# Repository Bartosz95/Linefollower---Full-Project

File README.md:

# Linefollowers

# Abstract 
Current repository contains three of my line follower projects.
Linefollower is a mobile robot which follows the line.
My robots were built for competitions so the main aim was to allow them to move fast.
Some of them were also remote controlled.
I've created these robots from top to bottom myself it means that I designed a board, created it, solder elements, create program for CPU and install it.

# Technologies
- KiCad
- STM32CubeMX
- Qt

# Description
As I mentioned current directory contains three robots
- BEBO - my first line follower which has PID algorithm
- LFANT - line follower which has spread encoders and mesure his speed
- Remote Controlled - this one is controlled by desktop remote app
To create these robots I had to do the same steps which I described below.

## Hardware
First I have to design a board. I've used a KiCad application to do it.
During this process I had to choose a CPU, engines, bridge for engine, battery, line sensors and all necessary elements.
I have chosen CPU STM32F051C8Tx because is enough small, 2 Pololu 10:1 engines, TB6612 bridge, Li-Pol 7,4V battery, line sensor KTIR0711s and depending on project AS5048A encoders or HC-06 bluetooth module.
Below you can see what it looks like designed boards ready to create.

In the next step I have to create this board and solder elements.
All

## Software
For creating software I decided to use the STM32CubeMX application.
It allows you to create programs for STM processors easily.
I assigned all necessary pins to the processor and created a controlled program.
When I finished programming it, I installed a program on robots by programator located on the STM32F4 board.
Created connection looks like below.

Ready robot looks like below.

# Desktop application
For a remote controlled robot I created a program in C++ Qt. 
The connection works through bluetooth. Program works below.
The main window of the program is split vertically.
On the left side you can see measurements from the line follower.
On the right you have a control panel.
If each sensor detects a black line the circle of the top will change to black.
Below grey rectangles you can see 0. When a robot is moving it shows speed in mps.
In the control panel you have 5 buttons.
The one on the top change remote controlling to automatic control by PID algorithm,
The next four allow remote control robots.

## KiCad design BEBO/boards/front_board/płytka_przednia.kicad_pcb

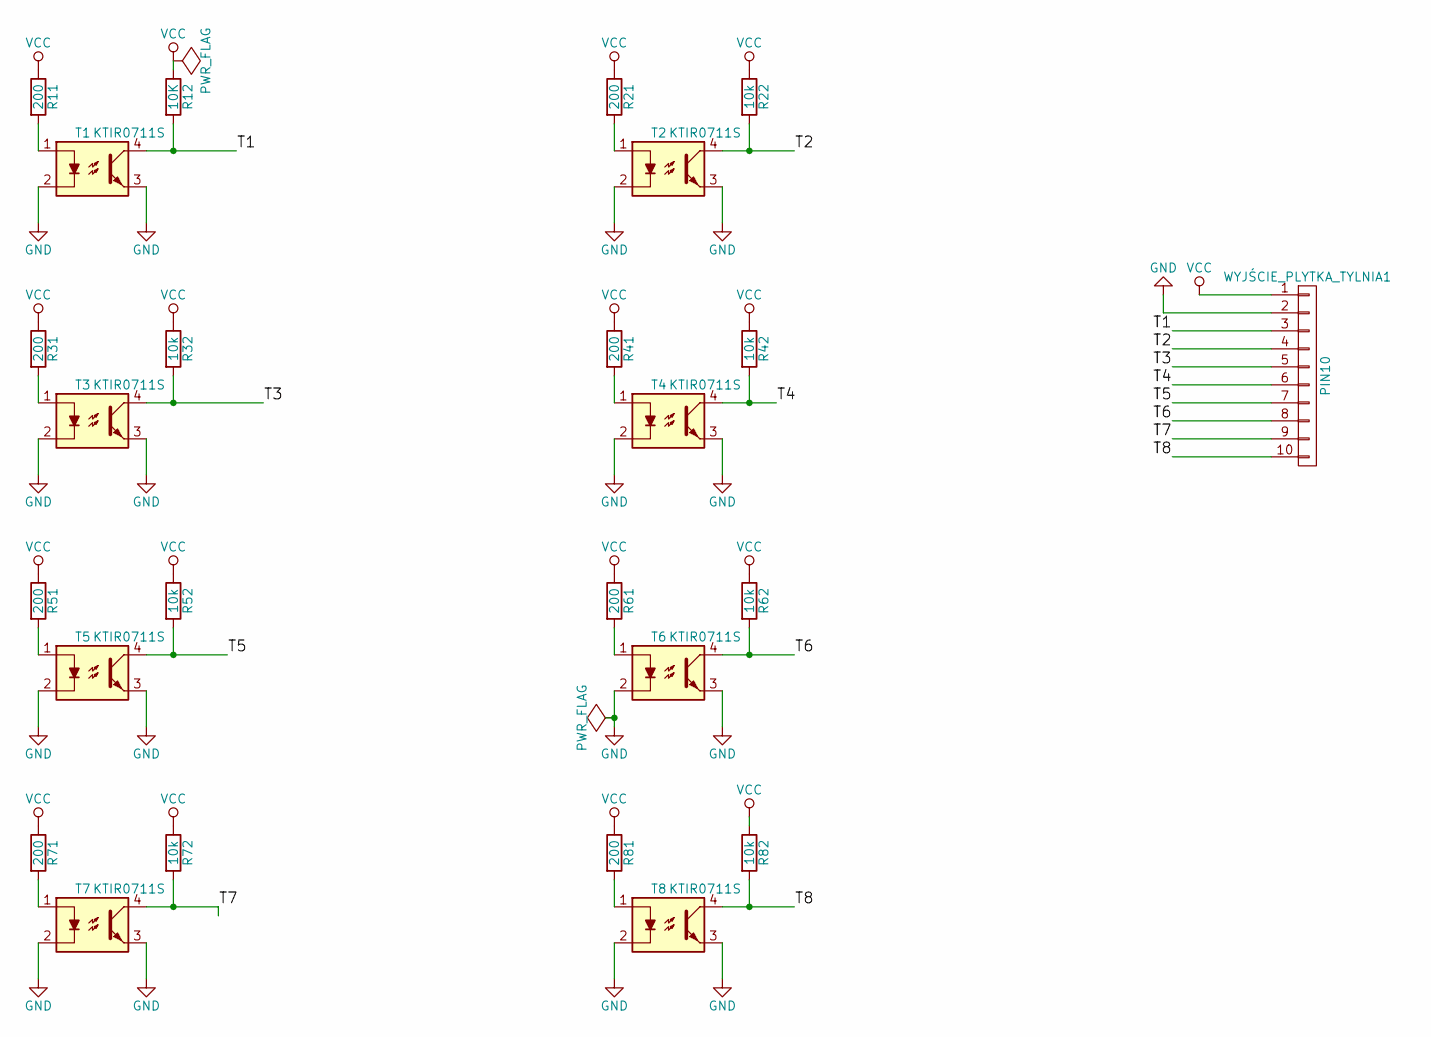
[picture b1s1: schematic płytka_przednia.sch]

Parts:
R11, R21, R31, R41, R51, R61, R71, R81: 200; R_0805_HandSoldering
R12: 10K; R_0805_HandSoldering
R22, R32, R42, R52, R62, R72, R82: 10k; R_0805_HandSoldering
T1, T2, T3, T4, T5, T6, T7, T8: KTIR0711S
WYJŚCIE_PLYTKA_TYLNIA1: PIN10; fpc_10_pin

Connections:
/T1: R12.2, T1.4, WYJŚCIE_PLYTKA_TYLNIA1.3
/T2: R22.2, T2.4, WYJŚCIE_PLYTKA_TYLNIA1.4
/T3: R32.2, T3.4, WYJŚCIE_PLYTKA_TYLNIA1.5
/T4: R42.2, T4.4, WYJŚCIE_PLYTKA_TYLNIA1.6
/T5: R52.2, T5.4, WYJŚCIE_PLYTKA_TYLNIA1.7
/T6: R62.2, T6.4, WYJŚCIE_PLYTKA_TYLNIA1.8
/T7: R72.2, T7.4, WYJŚCIE_PLYTKA_TYLNIA1.9
/T8: R82.2, T8.4, WYJŚCIE_PLYTKA_TYLNIA1.10
GND: T1.2, T1.3, T2.2, T2.3, T3.2, T3.3, T4.2, T4.3, T5.2, T5.3, T6.2, T6.3, T7.2, T7.3, T8.2, T8.3, WYJŚCIE_PLYTKA_TYLNIA1.2
unnamed: R11.2, T1.1
unnamed: R21.2, T2.1
unnamed: R31.2, T3.1
unnamed: R41.2, T4.1
unnamed: R51.2, T5.1
unnamed: R61.2, T6.1
unnamed: R71.2, T7.1
unnamed: R81.2, T8.1
VCC: R11.1, R12.1, R21.1, R22.1, R31.1, R32.1, R41.1, R42.1, R51.1, R52.1, R61.1, R62.1, R71.1, R72.1, R81.1, R82.1, WYJŚCIE_PLYTKA_TYLNIA1.1

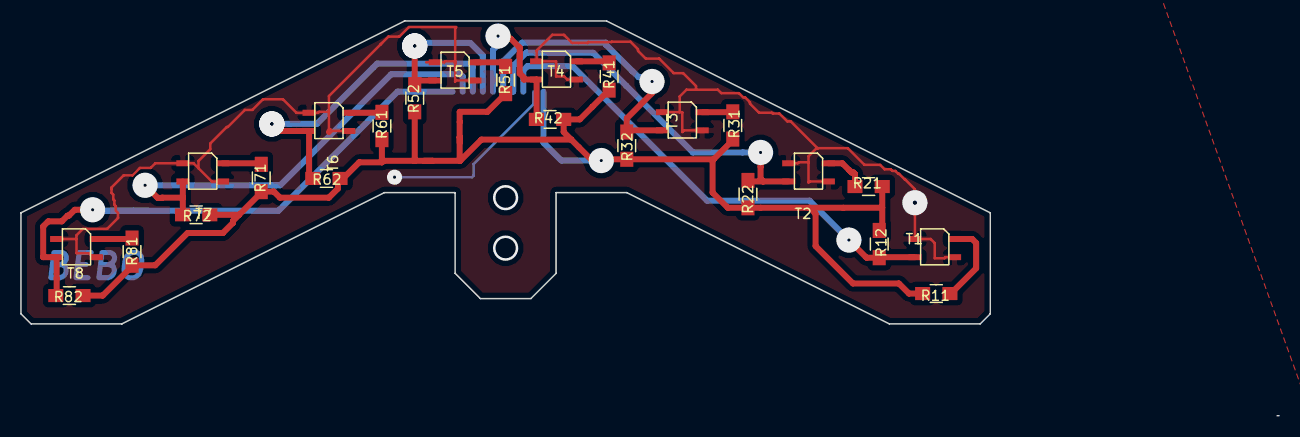
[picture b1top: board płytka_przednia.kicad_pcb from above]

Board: 2 copper layers, 124.6 x 39.1 mm, 25 parts (1 on the bottom side), 18 nets.

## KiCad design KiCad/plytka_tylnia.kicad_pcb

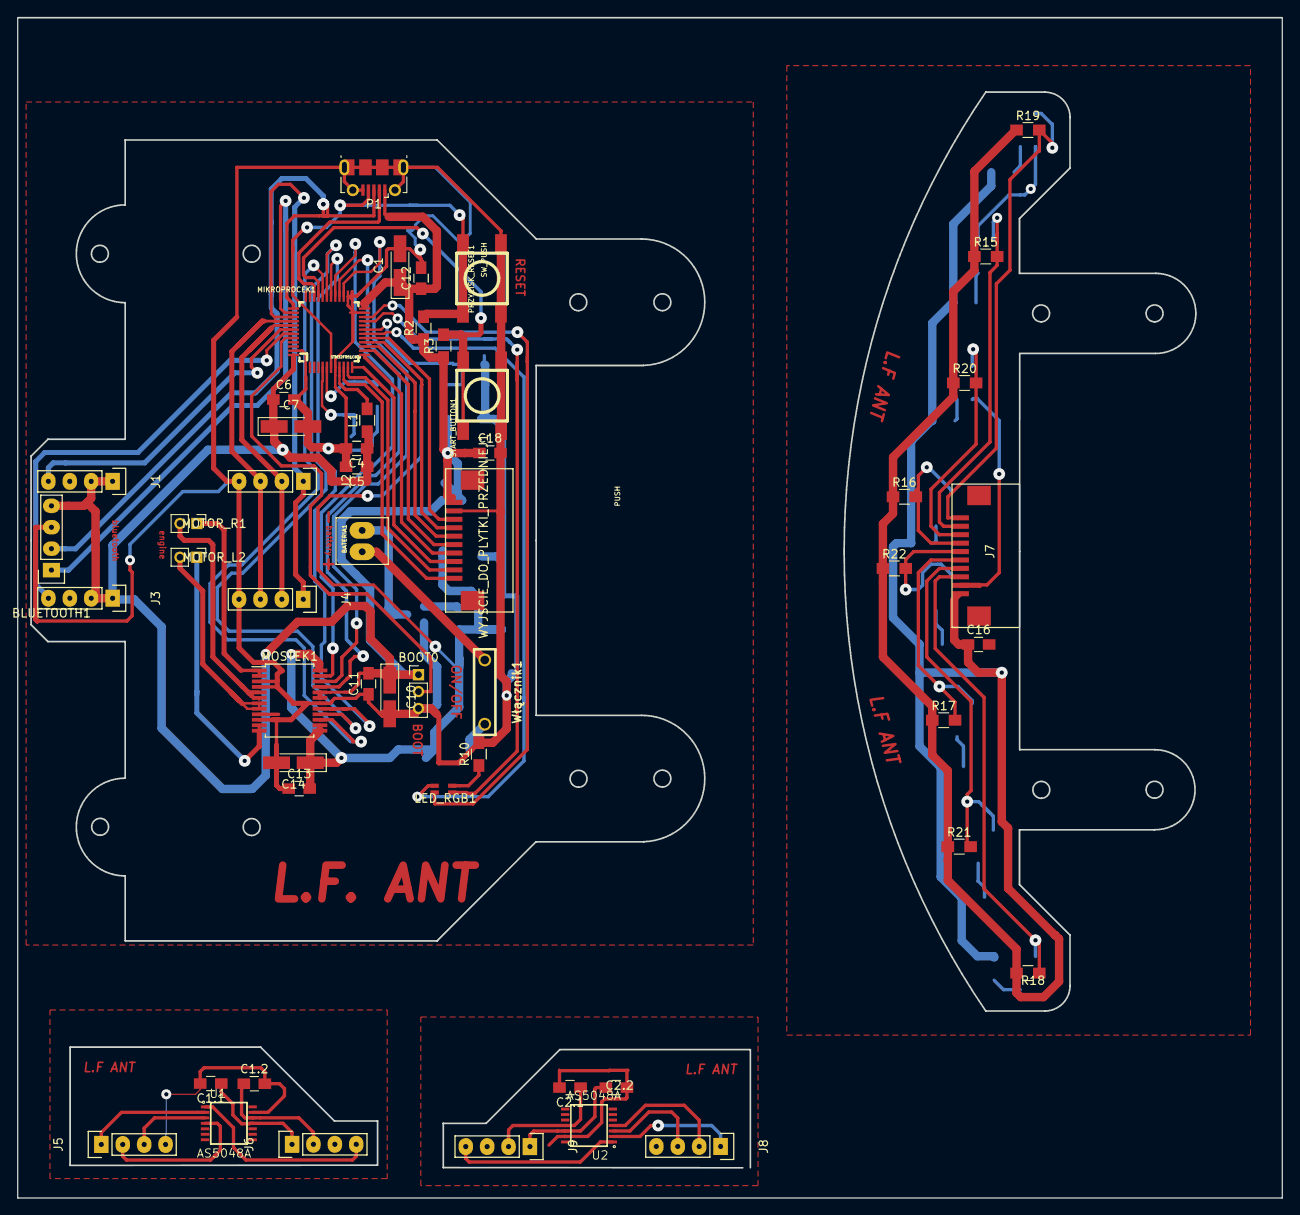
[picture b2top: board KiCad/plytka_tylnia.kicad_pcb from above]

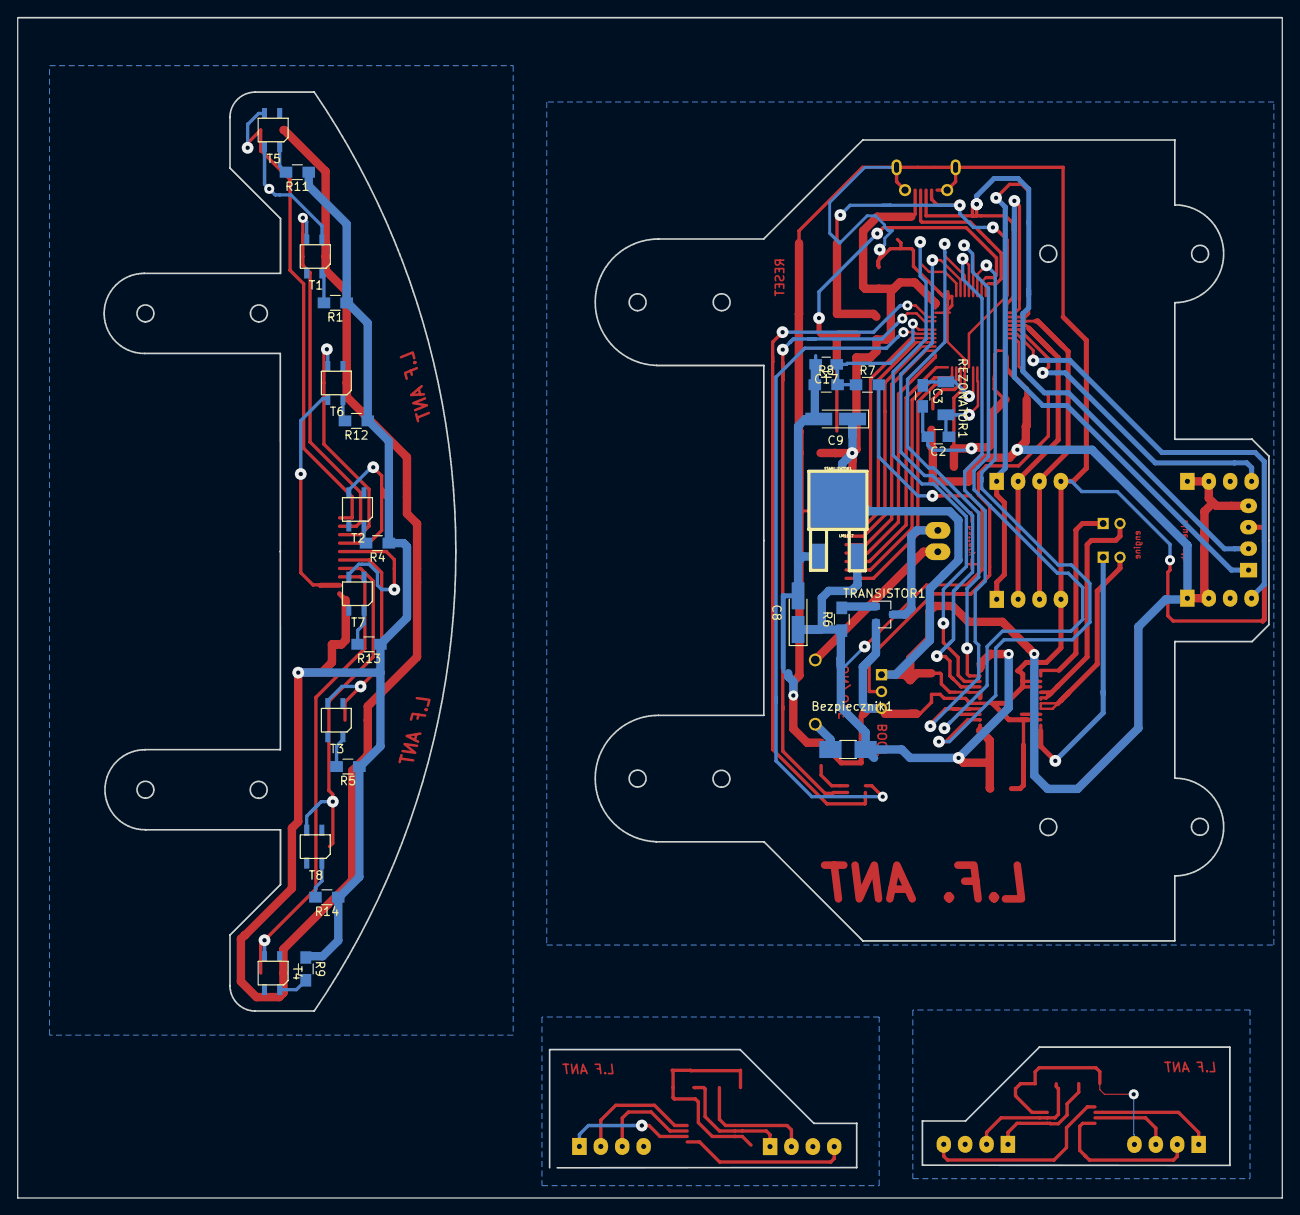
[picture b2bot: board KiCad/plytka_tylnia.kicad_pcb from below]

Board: 2 copper layers, 150.0 x 140.0 mm, 80 parts (28 on the bottom side), 72 nets.

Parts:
BATERIA1: LI-POL; zl_zasilania
BLUETOOTH1: PIN4; GoldPin_1x4
BOOT0: SWITCH; Pin_Header_Straight_1x03_Pitch2.00mm
Bezpiecznik1: Fuse ??; Fuse_SMD1206_HandSoldering
C1, C7: 4,7uF; CP_Tantalum_Case-A_EIA-3216-18_Hand
C1.1, C1.2, C2.1, C2.2, C16, C17: C; C_0805_HandSoldering
C2, C3: 22pF; C_0805_HandSoldering
C4: 10nF; C_0805_HandSoldering
C5: 1uF; C_0805_HandSoldering
C6, C11, C12, C13, C18: 100nF; C_0805_HandSoldering
C8, C9, C10, C14: 10uF; CP_Tantalum_Case-A_EIA-3216-18_Hand
J1, J2, J3, J4, J5, J6, J8, J9: CONN_01X04; GoldPin_1x4
J7: PIN10; fpc_10_pin
L1: 10uH; R_0805_HandSoldering
LED_RGB1: LED_CRGB; LED_RGB_0805
MIKROPROCEK1: STM32F051C8Tx; LQFP48
MOSTEK1: TB6612
MOTOR_L2: PIN2; Pin_Header_Straight_1x02_Pitch2.00mm
MOTOR_R1: PIN2; Pin_Header_Straight_1x02_Pitch2.00mm
P1: USB_OTG; USB_Micro-B_Molex-105017-0001
PRZYCISK_RESET1: SW_PUSH; SW_06_SMD
R1, R4, R5, R9, R11, R12, R13, R14: 200; R_0805_HandSoldering
R2, R3, R15, R16, R17, R18, R20, R21, R22: 10k; R_0805_HandSoldering
R6: 1k; R_0805_HandSoldering
R7: 51k; R_0805_HandSoldering
R8: 33k; R_0805_HandSoldering
R10: 220R; R_0805_HandSoldering
R19: 10K; R_0805_HandSoldering
REZONATOR1: HC49-S; Kwarc_SMD_Mini
STABILIZATOR1: LM1117; LM1117_TO-252
START_BUTTON1: PUSH; SW_06_SMD
T1, T2, T3, T4, T5, T6, T7, T8: KTIR0711S
TRANSISTOR1: BUZ11; SOT-23
U1, U2: AS5048A; SOP65P640X120-14N
WYJSCIE_DO_PLYTKI_PRZEDNIEJ1: PIN10; fpc_10_pin
Włącznik1: switch; dip_switch_1

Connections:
/3.31: C1.1.1, C1.2.1, J6.1, J6.2, U1.11, U1.12
/3.32: C2.1.1, C2.2.1, J9.1, J9.2, U2.11, U2.12
/BATERIA: Bezpiecznik1.1, C8.1, C13.2, C14.1, MOSTEK1.13, MOSTEK1.14, MOSTEK1.24, R6.1, R7.2, STABILIZATOR1.1
/BOOT0: BOOT0.2, MIKROPROCEK1.44
/CLK1: J5.1, U1.2
/CLK2: J8.1, U2.2
/GND1: C1.1.2, C1.2.2, J5.4, U1.13
/GND2: C2.1.2, C2.2.2, J8.4, U2.13
/LED_B: LED_RGB1.4, MIKROPROCEK1.18
/LED_G: LED_RGB1.3, MIKROPROCEK1.22
/LED_R: LED_RGB1.2, MIKROPROCEK1.21
/LIPOL_POMIAR: C17.1, MIKROPROCEK1.19, R7.1, R8.2
/L_1: MIKROPROCEK1.27, MOSTEK1.22
/L_2: MIKROPROCEK1.28, MOSTEK1.21
/L_PWM: MIKROPROCEK1.29, MOSTEK1.23
/MISO1: J5.3, U1.3
/MISO2: J8.3, U2.3
/MOSI1: J5.2, U1.4
/MOSI2: J8.2, U2.4
/RESET: MIKROPROCEK1.7, P1.4, PRZYCISK_RESET1.1, R2.2
/R_1: MIKROPROCEK1.31, MOSTEK1.16
/R_2: MIKROPROCEK1.30, MOSTEK1.17
/R_PWM: MIKROPROCEK1.32, MOSTEK1.15
/SPI1_CLK: J2.1, J4.1, MIKROPROCEK1.39
/SPI1_MISO: J2.3, J4.3, MIKROPROCEK1.40
/SPI1_MOSI: J2.2, J4.2, MIKROPROCEK1.41
/SPI1_SS1: J1.4, MIKROPROCEK1.42
/SPI1_SS2: J3.4, MIKROPROCEK1.43
/SS1: J6.4, U1.1
/SS2: J9.4, U2.1
/SWCLK: BLUETOOTH1.2, MIKROPROCEK1.37, P1.3
/SWDIO: MIKROPROCEK1.34, P1.2
/T1: MIKROPROCEK1.10, WYJSCIE_DO_PLYTKI_PRZEDNIEJ1.1
/T1P: J7.10, R19.2, T5.4
/T2: MIKROPROCEK1.11, WYJSCIE_DO_PLYTKI_PRZEDNIEJ1.2
/T2P: J7.9, R15.2, T1.4
/T3: MIKROPROCEK1.12, WYJSCIE_DO_PLYTKI_PRZEDNIEJ1.3
/T3P: J7.8, R20.2, T6.4
/T4: MIKROPROCEK1.13, WYJSCIE_DO_PLYTKI_PRZEDNIEJ1.4
/T4P: J7.7, R16.2, T2.4
/T5: MIKROPROCEK1.14, WYJSCIE_DO_PLYTKI_PRZEDNIEJ1.5
/T5P: J7.6, R22.2, T7.4
/T6: MIKROPROCEK1.15, WYJSCIE_DO_PLYTKI_PRZEDNIEJ1.6
/T6P: J7.5, R17.2, T3.4
/T7: MIKROPROCEK1.16, WYJSCIE_DO_PLYTKI_PRZEDNIEJ1.7
/T7P: J7.4, R21.2, T8.4
/T8: MIKROPROCEK1.17, WYJSCIE_DO_PLYTKI_PRZEDNIEJ1.8
/T8P: J7.3, R18.2, T4.4
/USART_RX: BLUETOOTH1.1, MIKROPROCEK1.38
GND: BLUETOOTH1.3, BOOT0.3, C1.2, C2.2, C3.2, C4.2, C5.2, C6.2, C7.2, C8.2, C9.2, C10.2, C11.1, C12.2, C13.1, C14.2, C16.2, C17.2, C18.2, J2.4, J4.4, J7.2, MIKROPROCEK1.1, MIKROPROCEK1.8, MIKROPROCEK1.23, MIKROPROCEK1.25, MIKROPROCEK1.26, MIKROPROCEK1.47, MOSTEK1.3, MOSTEK1.4, MOSTEK1.9, MOSTEK1.10, MOSTEK1.18, P1.5, P1.6, PRZYCISK_RESET1.2, R8.1, R10.2, STABILIZATOR1.3, START_BUTTON1.1, T1.2, T1.3, T2.2, T2.3, T3.2, T3.3, T4.2, T4.3, T5.2, T5.3, T6.2, T6.3, T7.2, T7.3, T8.2, T8.3, TRANSISTOR1.2, WYJSCIE_DO_PLYTKI_PRZEDNIEJ1.9
unnamed: BATERIA1.1, TRANSISTOR1.3
unnamed: BATERIA1.2, Włącznik1.1
unnamed: Bezpiecznik1.2, Włącznik1.2
unnamed: C2.1, MIKROPROCEK1.5, REZONATOR1.2
unnamed: C3.1, MIKROPROCEK1.6, REZONATOR1.1
unnamed: L1.2, MIKROPROCEK1.9
unnamed: LED_RGB1.1, R10.1
unnamed: MIKROPROCEK1.33, R3.2, START_BUTTON1.2
unnamed: MOSTEK1.1, MOSTEK1.2, MOTOR_R1.1
unnamed: MOSTEK1.5, MOSTEK1.6, MOTOR_R1.2
unnamed: MOSTEK1.7, MOSTEK1.8, MOTOR_L2.2
unnamed: MOSTEK1.11, MOSTEK1.12, MOTOR_L2.1
unnamed: R1.2, T1.1
unnamed: R4.2, T2.1
unnamed: R5.2, T3.1
unnamed: R6.2, TRANSISTOR1.1
unnamed: R9.2, T4.1
unnamed: R11.2, T5.1
unnamed: R12.2, T6.1
unnamed: R13.2, T7.1
unnamed: R14.2, T8.1
VCC: BLUETOOTH1.4, BOOT0.1, C1.1, C4.1, C5.1, C6.1, C7.1, C9.1, C10.1, C11.2, C12.1, C16.1, C18.1, J1.1, J1.2, J3.1, J3.2, J7.1, L1.1, MIKROPROCEK1.24, MIKROPROCEK1.48, MOSTEK1.19, MOSTEK1.20, P1.1, R1.1, R2.1, R3.1, R4.1, R5.1, R9.1, R11.1, R12.1, R13.1, R14.1, R15.1, R16.1, R17.1, R18.1, R19.1, R20.1, R21.1, R22.1, STABILIZATOR1.2, WYJSCIE_DO_PLYTKI_PRZEDNIEJ1.10

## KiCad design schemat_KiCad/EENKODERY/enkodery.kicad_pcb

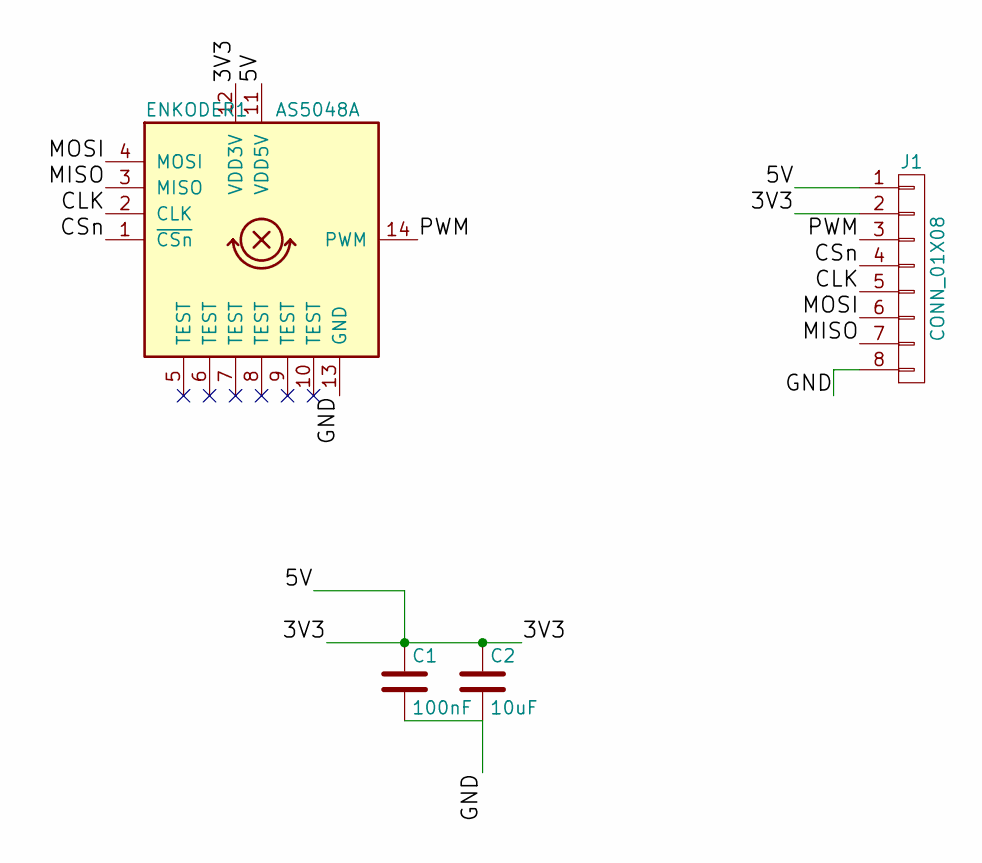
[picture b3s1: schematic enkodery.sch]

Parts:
C1: 100nF; C_0805_HandSoldering
C2: 10uF; C_0805_HandSoldering
ENKODER1: AS5048A; SOP65P640X120-14N
J1: CONN_01X08; Pin_Header_Straight_1x08_Pitch2.00mm

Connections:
/3V3: C1.1, C2.1, ENKODER1.11 (VDD5V), ENKODER1.12 (VDD3V), J1.1, J1.2
/CLK: ENKODER1.2 (CLK), J1.5
/CSn: ENKODER1.1 (~CSn), J1.4
/GND: C1.2, C2.2, ENKODER1.13 (GND), J1.8
/MISO: ENKODER1.3 (MISO), J1.7
/MOSI: ENKODER1.4 (MOSI), J1.6
/PWM: ENKODER1.14 (PWM), J1.3

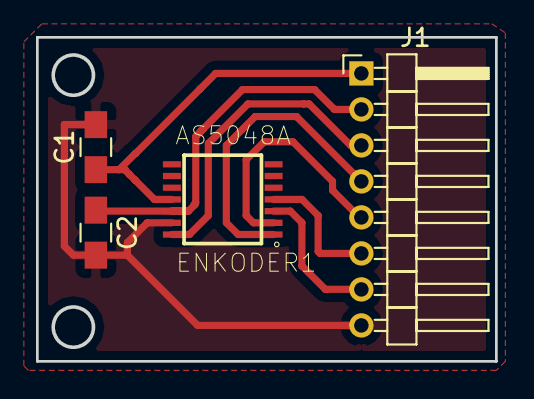
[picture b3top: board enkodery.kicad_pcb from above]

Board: 2 copper layers, 25.4 x 18.0 mm, 4 parts (0 on the bottom side), 7 nets.

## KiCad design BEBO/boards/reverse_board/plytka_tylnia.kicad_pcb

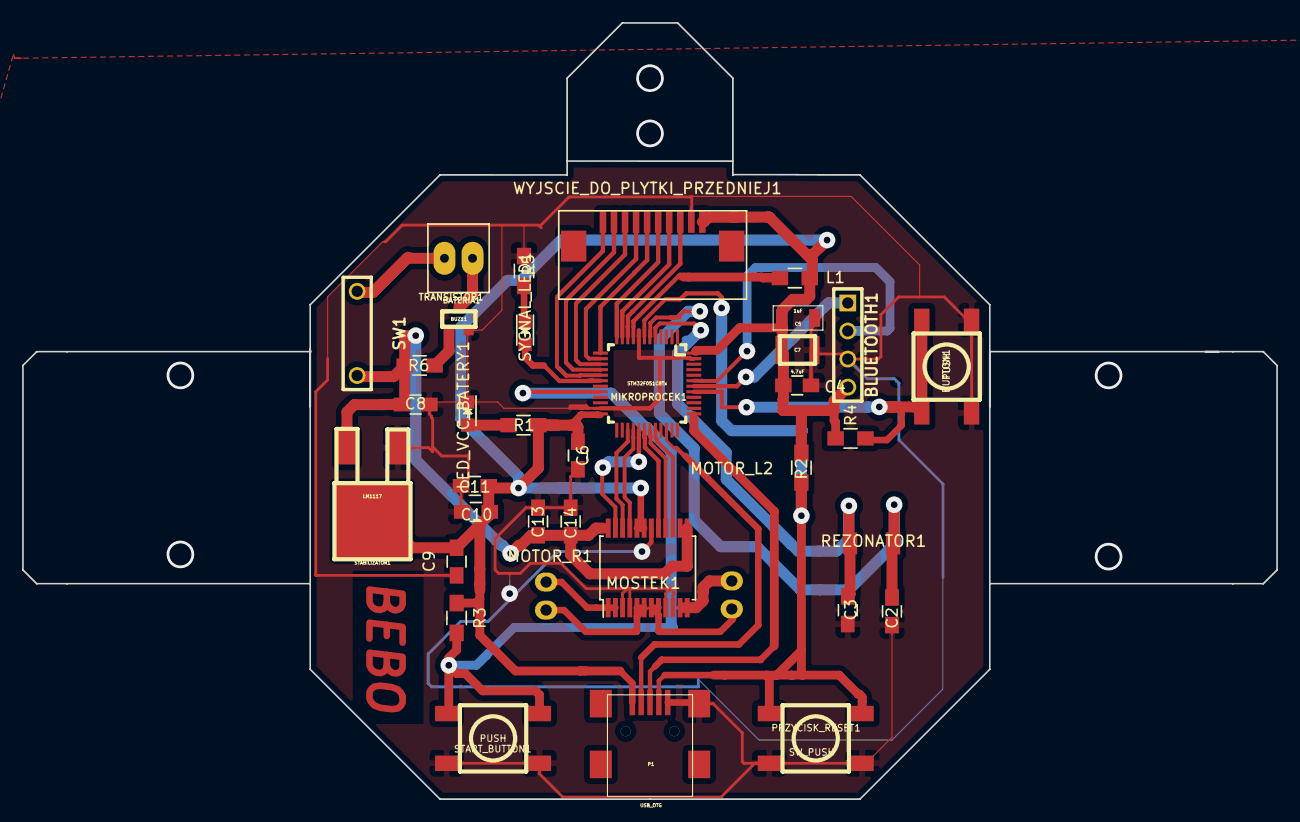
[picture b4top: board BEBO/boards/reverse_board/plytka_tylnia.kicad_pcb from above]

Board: 2 copper layers, 113.5 x 70.2 mm, 36 parts (0 on the bottom side), 37 nets.

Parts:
BATERIA1: LI-POL; zl_zasilania
BLUETOOTH1: PIN4; pin_array_4x1
BUTTON1: PUSH; SW_06_SMD
C2, C3: 22pF; C_0805_HandSoldering
C4: 10nF; C_0805_HandSoldering
C5: 1uF; 1206
C6: 100nF; C_0805_HandSoldering
C7: 4,7uF; 1210
C8, C9, C11, C14: 10uF; C_0805_HandSoldering
C10: 1uF; C_0805_HandSoldering
C13: 0.1uF; C_0805_HandSoldering
L1: 10uH; R_0805_HandSoldering
LED_VCC_BATERY1: LED_GREEN; LED_0805
MIKROPROCEK1: STM32F051C8Tx; LQFP48
MOSTEK1: TB6612
MOTOR_L2: PIN2; silnik
MOTOR_R1: PIN2; silnik
P1: USB_OTG; USB-MINI-B-SMD
PRZYCISK_RESET1: SW_PUSH; SW_06_SMD
R1, R5: 200; R_0805_HandSoldering
R2, R3, R4: 10k; R_0805_HandSoldering
R6: 1k; R_0805_HandSoldering
REZONATOR1: HC49-S; Kwarc_SMD_Mini
STABILIZATOR1: LM1117; LM1117_TO-252
START_BUTTON1: PUSH; SW_06_SMD
SW1: SPST; dip_switch_1
SYGNAL_LED1: LED_BLUE; LED_0805
TRANSISTOR1: BUZ11; SOT23-3
WYJSCIE_DO_PLYTKI_PRZEDNIEJ1: PIN10; fpc_10_pin

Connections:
/BATERIA: C8.1, C13.2, C14.1, MOSTEK1.13, MOSTEK1.14, MOSTEK1.24, R6.2, STABILIZATOR1.1, SW1.2
/L_IN1: MIKROPROCEK1.27, MOSTEK1.22
/L_IN2: MIKROPROCEK1.28, MOSTEK1.21
/L_PWM: MIKROPROCEK1.29, MOSTEK1.23
/RESET: MIKROPROCEK1.7, P1.4, PRZYCISK_RESET1.1, R2.2
/R_IN1: MIKROPROCEK1.31, MOSTEK1.16
/R_IN2: MIKROPROCEK1.30, MOSTEK1.17
/R_PWM: MIKROPROCEK1.32, MOSTEK1.15
/SWCLK: MIKROPROCEK1.37, P1.3
/SWDIO: MIKROPROCEK1.34, P1.2
/T1: MIKROPROCEK1.10, WYJSCIE_DO_PLYTKI_PRZEDNIEJ1.8
/T2: MIKROPROCEK1.11, WYJSCIE_DO_PLYTKI_PRZEDNIEJ1.7
/T3: MIKROPROCEK1.12, WYJSCIE_DO_PLYTKI_PRZEDNIEJ1.6
/T4: MIKROPROCEK1.13, WYJSCIE_DO_PLYTKI_PRZEDNIEJ1.5
/T5: MIKROPROCEK1.14, WYJSCIE_DO_PLYTKI_PRZEDNIEJ1.4
/T6: MIKROPROCEK1.15, WYJSCIE_DO_PLYTKI_PRZEDNIEJ1.3
/T7: MIKROPROCEK1.16, WYJSCIE_DO_PLYTKI_PRZEDNIEJ1.2
/T8: MIKROPROCEK1.17, WYJSCIE_DO_PLYTKI_PRZEDNIEJ1.1
/USART_RX: BLUETOOTH1.1, MIKROPROCEK1.42
/USART_TX: BLUETOOTH1.2, MIKROPROCEK1.43
GND: BLUETOOTH1.3, BUTTON1.1, C2.2, C3.2, C4.2, C5.2, C6.2, C7.2, C8.2, C9.2, C10.2, C11.1, C13.1, C14.2, LED_VCC_BATERY1.1, MIKROPROCEK1.8, MIKROPROCEK1.23, MIKROPROCEK1.47, MOSTEK1.3, MOSTEK1.4, MOSTEK1.9, MOSTEK1.10, MOSTEK1.18, P1.5, P1.6, PRZYCISK_RESET1.2, R5.2, STABILIZATOR1.3, START_BUTTON1.1, TRANSISTOR1.2, WYJSCIE_DO_PLYTKI_PRZEDNIEJ1.9
unnamed: BATERIA1.1, TRANSISTOR1.3
unnamed: BATERIA1.2, SW1.1
unnamed: BUTTON1.2, MIKROPROCEK1.41, R4.2
unnamed: C3.1, MIKROPROCEK1.5, REZONATOR1.1
unnamed: C2.1, MIKROPROCEK1.6, REZONATOR1.2
unnamed: R6.1, TRANSISTOR1.1
unnamed: L1.2, MIKROPROCEK1.9
unnamed: LED_VCC_BATERY1.2, R1.1
unnamed: MIKROPROCEK1.20, R3.2, START_BUTTON1.2
unnamed: MIKROPROCEK1.18, SYGNAL_LED1.2
unnamed: MOSTEK1.1, MOSTEK1.2, MOTOR_R1.1
unnamed: MOSTEK1.5, MOSTEK1.6, MOTOR_R1.2
unnamed: MOSTEK1.7, MOSTEK1.8, MOTOR_L2.2
unnamed: MOSTEK1.11, MOSTEK1.12, MOTOR_L2.1
unnamed: R5.1, SYGNAL_LED1.1
VCC: BLUETOOTH1.4, C4.1, C5.1, C6.1, C7.1, C9.1, C10.1, C11.2, L1.1, MIKROPROCEK1.24, MIKROPROCEK1.48, MOSTEK1.19, MOSTEK1.20, P1.1, R1.2, R2.1, R3.1, R4.1, STABILIZATOR1.2, WYJSCIE_DO_PLYTKI_PRZEDNIEJ1.10

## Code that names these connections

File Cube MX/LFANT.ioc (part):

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Mcu.Name=STM32F051C8Tx
Mcu.Package=LQFP48
Mcu.UserName=STM32F051C8Tx
PA0.GPIOParameters=GPIO_Label
PA0.GPIO_Label=T1
PA0.Mode=IN0
PA0.Signal=ADC_IN0
PA1.GPIOParameters=GPIO_Label
PA1.GPIO_Label=T2
PA1.Mode=IN1
PA1.Signal=ADC_IN1
PA10.GPIOParameters=GPIO_Label
PA10.GPIO_Label=R_TYL
PA10.Signal=GPIO_Output
PA11.GPIOParameters=GPIO_Label
PA11.GPIO_Label=R_PWM
PA11.Signal=S_TIM1_CH4
PA12.GPIOParameters=GPIO_Label
PA12.GPIO_Label=START_BUTTON
PA12.Signal=GPXTI12
PA14.Mode=Asynchronous
PA14.Signal=USART2_TX
PA15.Mode=Asynchronous
PA15.Signal=USART2_RX
PA2.GPIOParameters=GPIO_Label
PA2.GPIO_Label=T3
PA2.Mode=IN2
PA2.Signal=ADC_IN2
PA3.GPIOParameters=GPIO_Label
PA3.GPIO_Label=T4
PA3.Mode=IN3
PA3.Signal=ADC_IN3
PA4.GPIOParameters=GPIO_Label
PA4.GPIO_Label=T5
PA4.Mode=IN4
PA4.Signal=ADC_IN4
PA5.GPIOParameters=GPIO_Label
PA5.GPIO_Label=T6
PA5.Mode=IN5
PA5.Signal=ADC_IN5
PA6.GPIOParameters=GPIO_Label
PA6.GPIO_Label=T7
PA6.Mode=IN6
PA6.Signal=ADC_IN6
PA7.GPIOParameters=GPIO_Label
PA7.GPIO_Label=T8
PA7.Mode=IN7
PA7.Signal=ADC_IN7
PA8.GPIOParameters=GPIO_Label
PA8.GPIO_Label=L_PWM
PA8.Signal=S_TIM1_CH1
PA9.GPIOParameters=GPIO_Label
PA9.GPIO_Label=R_PRZOD
PA9.Signal=GPIO_Output
PB0.GPIOParameters=GPIO_Label
PB0.GPIO_Label=LED_B
PB0.Signal=S_TIM3_CH3
PB1.GPIOParameters=GPIO_Label
PB1.GPIO_Label=LIPOL_POMIAR
PB1.Mode=IN9
PB1.Signal=ADC_IN9
PB10.GPIOParameters=GPIO_Label
PB10.GPIO_Label=LED_R
PB10.Signal=S_TIM2_CH3
PB11.GPIOParameters=GPIO_Label
PB11.GPIO_Label=LED_G
PB11.Signal=S_TIM2_CH4
PB14.GPIOParameters=GPIO_Label
PB14.GPIO_Label=L_TYL
PB14.Signal=GPIO_Output
PB15.GPIOParameters=GPIO_Label
PB15.GPIO_Label=L_PRZOD
PB15.Signal=GPIO_Output
PB3.Mode=Full_Duplex_Master
PB3.Signal=SPI1_SCK
PB4.Mode=Full_Duplex_Master
PB4.Signal=SPI1_MISO
PB5.Mode=Full_Duplex_Master
PB5.Signal=SPI1_MOSI
PB6.GPIOParameters=GPIO_Label
PB6.GPIO_Label=SPI1_SS1
PB6.Signal=GPIO_Output
PB7.GPIOParameters=GPIO_Label
PB7.GPIO_Label=SPI1_SS2
PB7.Signal=GPIO_Output
PF0-OSC_IN.GPIOParameters=GPIO_Label
PF0-OSC_IN.GPIO_Label=OSC_IN
PF0-OSC_IN.Mode=HSE-External-Oscillator
PF0-OSC_IN.Signal=RCC_OSC_IN
PF1-OSC_OUT.GPIOParameters=GPIO_Label
PF1-OSC_OUT.GPIO_Label=OSC_OUT
PF1-OSC_OUT.Mode=HSE-External-Oscillator
PF1-OSC_OUT.Signal=RCC_OSC_OUT
RCC.HSEState=RCC_HSE_ON
RCC.HSE_VALUE=8000000
RCC.SYSCLKFreq_VALUE=48000000
RCC.SYSCLKSource=RCC_SYSCLKSOURCE_PLLCLK

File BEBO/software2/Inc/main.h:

/**
  ******************************************************************************
  * File Name          : main.h
  * Description        : This file contains the common defines of the application
  ******************************************************************************
  *
  * COPYRIGHT(c) 2017 STMicroelectronics
  *
  * Redistribution and use in source and binary forms, with or without modification,
  * are permitted provided that the following conditions are met:
  *   1. Redistributions of source code must retain the above copyright notice,
  *      this list of conditions and the following disclaimer.
  *   2. Redistributions in binary form must reproduce the above copyright notice,
  *      this list of conditions and the following disclaimer in the documentation
  *      and/or other materials provided with the distribution.
  *   3. Neither the name of STMicroelectronics nor the names of its contributors
  *      may be used to endorse or promote products derived from this software
  *      without specific prior written permission.
  *
  * THIS SOFTWARE IS PROVIDED BY THE COPYRIGHT HOLDERS AND CONTRIBUTORS "AS IS"
  * AND ANY EXPRESS OR IMPLIED WARRANTIES, INCLUDING, BUT NOT LIMITED TO, THE
  * IMPLIED WARRANTIES OF MERCHANTABILITY AND FITNESS FOR A PARTICULAR PURPOSE ARE
  * DISCLAIMED. IN NO EVENT SHALL THE COPYRIGHT HOLDER OR CONTRIBUTORS BE LIABLE
  * FOR ANY DIRECT, INDIRECT, INCIDENTAL, SPECIAL, EXEMPLARY, OR CONSEQUENTIAL
  * DAMAGES (INCLUDING, BUT NOT LIMITED TO, PROCUREMENT OF SUBSTITUTE GOODS OR
  * SERVICES; LOSS OF USE, DATA, OR PROFITS; OR BUSINESS INTERRUPTION) HOWEVER
  * CAUSED AND ON ANY THEORY OF LIABILITY, WHETHER IN CONTRACT, STRICT LIABILITY,
  * OR TORT (INCLUDING NEGLIGENCE OR OTHERWISE) ARISING IN ANY WAY OUT OF THE USE
  * OF THIS SOFTWARE, EVEN IF ADVISED OF THE POSSIBILITY OF SUCH DAMAGE.
  *
  ******************************************************************************
  */
/* Define to prevent recursive inclusion -------------------------------------*/
#ifndef __MAIN_H
#define __MAIN_H
  /* Includes ------------------------------------------------------------------*/

/* USER CODE BEGIN Includes */

/* USER CODE END Includes */

/* Private define ------------------------------------------------------------*/

#define OSC_IN_Pin GPIO_PIN_0
#define OSC_IN_GPIO_Port GPIOF
#define OSC_OUT_Pin GPIO_PIN_1
#define OSC_OUT_GPIO_Port GPIOF
#define T1_Pin GPIO_PIN_0
#define T1_GPIO_Port GPIOA
#define T2_Pin GPIO_PIN_1
#define T2_GPIO_Port GPIOA
#define T3_Pin GPIO_PIN_2
#define T3_GPIO_Port GPIOA
#define T4_Pin GPIO_PIN_3
#define T4_GPIO_Port GPIOA
#define T5_Pin GPIO_PIN_4
#define T5_GPIO_Port GPIOA
#define T6_Pin GPIO_PIN_5
#define T6_GPIO_Port GPIOA
#define T7_Pin GPIO_PIN_6
#define T7_GPIO_Port GPIOA
#define T8_Pin GPIO_PIN_7
#define T8_GPIO_Port GPIOA
#define LED_Pin GPIO_PIN_0
#define LED_GPIO_Port GPIOB
#define START_BUTTON_Pin GPIO_PIN_2
#define START_BUTTON_GPIO_Port GPIOB
#define L_TYL_Pin GPIO_PIN_14
#define L_TYL_GPIO_Port GPIOB
#define L_PRZOD_Pin GPIO_PIN_15
#define L_PRZOD_GPIO_Port GPIOB
#define L_PWM_Pin GPIO_PIN_8
#define L_PWM_GPIO_Port GPIOA
#define R_PRZOD_Pin GPIO_PIN_9
#define R_PRZOD_GPIO_Port GPIOA
#define R_TYL_Pin GPIO_PIN_10
#define R_TYL_GPIO_Port GPIOA
#define R_PWM_Pin GPIO_PIN_11
#define R_PWM_GPIO_Port GPIOA
#define BUTTON_Pin GPIO_PIN_5
#define BUTTON_GPIO_Port GPIOB
#define USART_TX_Pin GPIO_PIN_6
#define USART_TX_GPIO_Port GPIOB
#define USART_RX_Pin GPIO_PIN_7
#define USART_RX_GPIO_Port GPIOB

/* USER CODE BEGIN Private defines */

/* USER CODE END Private defines */

/**
  * @}
  */ 

/**
  * @}
*/ 

#endif /* __MAIN_H */
/************************ (C) COPYRIGHT STMicroelectronics *****END OF FILE****/

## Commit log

2017-03-29 README.md created online with Bitbucket
2017-03-29 no message
2017-03-30 bez enkoderow
2017-03-30 turbina
2017-03-31 Raport 1
2017-04-05 zrobiony przełącznik boot0
2017-04-15 PCB-enkodery
2017-04-17 tył do druku
2017-04-17 nazwy przyciskow
2017-04-17 warstwa dolna okrag
2017-04-18 wejscie turbiny tylem
2017-04-24 poprawiony echo/trig
2017-04-26 Usuniecie zlacza 3x2
2017-05-02 zabezpieczenie przed odwrotną polaryzacją, ścieżki spi 0.6 , zwykle 0.4 zasilanie 1
2017-05-08 kondensatory spolaryzowane na tantalowe
2017-05-08 lista czesci
2017-05-08 skompletowane czesci, wybrane rezystory, kondensator przy wejsciu
2017-05-09 zamówienie z elektroparku
2017-05-15 archiwum ze złego projektu + drukowanie
2017-05-15 skończona płytka bez turbiny do wydruku
2017-05-22 poprawiona, odchudzona, zaokraglona
2017-05-22 zmniejszony obwod plytki
2017-05-23 zmienione przelotki na 1,4/0,5
2017-05-25 raster goldpin na 2,54, scieżki wokół procka i mostka na 0,3 mm,
2017-05-25 plik z modyfikacjami, nowy projekt cube
2017-06-02 dodanie mocowania magnesow w inventorze
2022-08-28 Add README
